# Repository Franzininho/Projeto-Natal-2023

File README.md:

# Projeto Natal 2023 Comunidade Franzininho

Esse é um projeto de placa decorativa de natal baseada no MCU Risc V CH32V003

## Requisitos 
 - MCU CH32V003F4P6
 - Alimentação por bateria CR2032
 - Animação em LEDs ou outra interface gráfica
 - Projeto no Kicad
 - Outros: Botão, buzzer, etc

## Como Participar?
1. Crie um fork desse projeto base.
2. Faça o seu Desing
3. Crie uma pequena documentação para explicar o seu projeto
4. Envie seu projeto para a comunidade Franzininho

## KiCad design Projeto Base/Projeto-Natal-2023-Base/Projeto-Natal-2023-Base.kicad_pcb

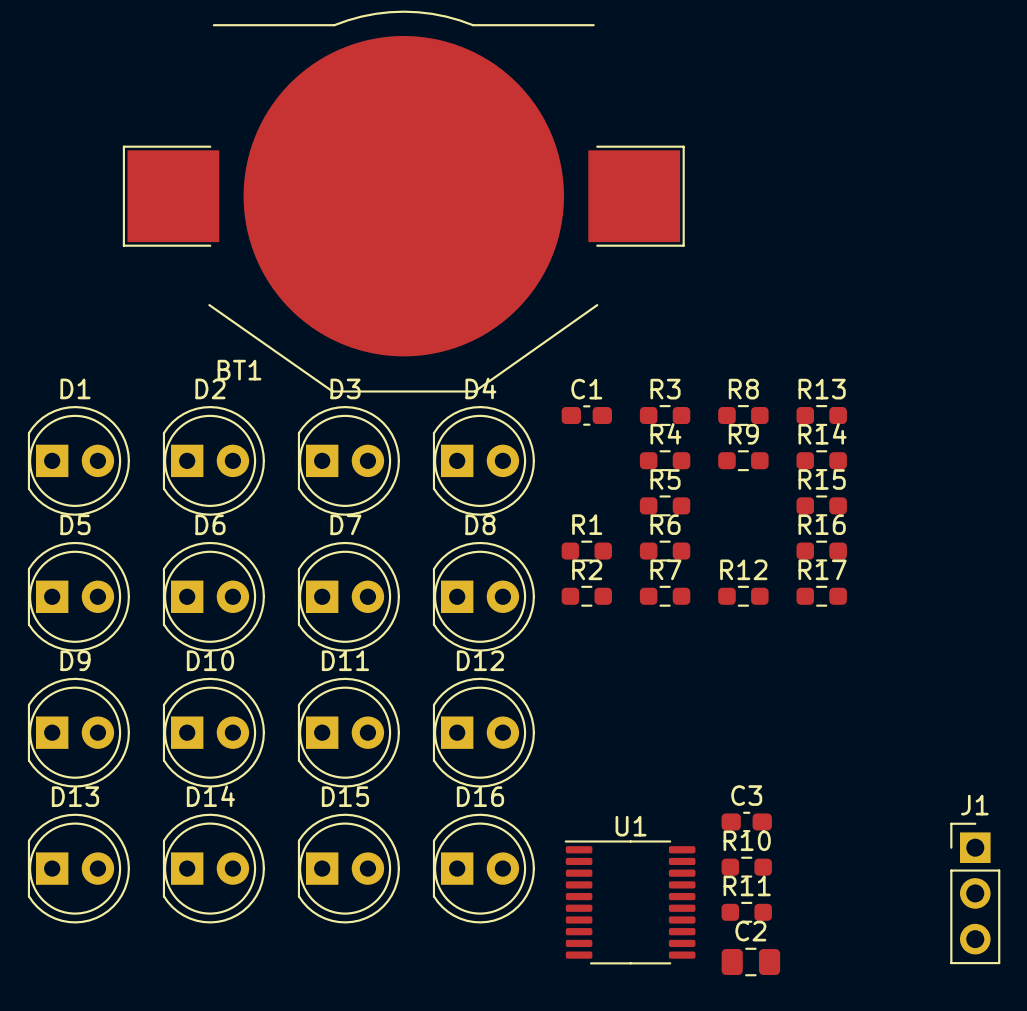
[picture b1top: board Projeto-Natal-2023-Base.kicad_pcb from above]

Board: 2 copper layers, 39 parts (0 on the bottom side), 34 nets, no tracks yet.

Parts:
BT1: Battery_Cell; BatteryHolder_Keystone_3002_1x2032
C1, C3: 100nF; C_0603_1608Metric_Pad1.08x0.95mm_HandSolder
C2: 10uF; C_0805_2012Metric_Pad1.18x1.45mm_HandSolder
D1, D2, D3, D4: LED R; LED_D5.0mm
D5, D6, D7, D8: LED G; LED_D5.0mm
D9, D10, D11, D12: LED B; LED_D5.0mm
D13, D14, D15, D16: LED Y; LED_D5.0mm
J1: Conn_01x03_Pin; PinHeader_1x03_P2.54mm_Vertical
R1: 10K; R_0603_1608Metric_Pad0.98x0.95mm_HandSolder
R2, R3, R4, R5, R6, R7, R8, R9, R10, R11, R12, R13, R14, R15, R16, R17: 1K; R_0603_1608Metric_Pad0.98x0.95mm_HandSolder
U1: CH32V003F4P6; TSSOP-20_4.4x6.5mm_P0.65mm

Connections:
+3V3: BT1.1 (+), C2.1, C3.2, J1.1, R1.1, U1.9 (VDD)
GND: BT1.2 (-), C1.1, C2.2, C3.1, D1.1 (K), D2.1 (K), D3.1 (K), D4.1 (K), D5.1 (K), D6.1 (K), D7.1 (K), D8.1 (K), D9.1 (K), D10.1 (K), D11.1 (K), D12.1 (K), D13.1 (K), D14.1 (K), D15.1 (K), D16.1 (K), J1.2, U1.7 (VSS)
LED1: D1.2 (A), R2.1
LED2: D5.2 (A), R3.1
LED3: D9.2 (A), R4.1
LED4: D13.2 (A), R5.1
LED5: D2.2 (A), R6.1
LED6: D6.2 (A), R7.1
LED7: D10.2 (A), R8.1
LED8: D14.2 (A), R9.1
LED11: D11.2 (A), R10.2, R11.2, R12.2
LED12: D15.2 (A), R13.2
LED13: D4.2 (A), R14.2
LED14: D8.2 (A), R15.2
LED15: D12.2 (A), R16.2
LED16: D16.2 (A), R17.2
unnamed: C1.2, R1.2, U1.4 (NRST/PD7)
unnamed: R2.2, U1.5 (OSC_IN/PA1)
unnamed: R3.2, U1.6 (OSC_OUT/PA2)
unnamed: R10.1, U1.10 (PC0)
unnamed: R11.1, U1.11 (PC1)
unnamed: R12.1, U1.12 (PC2)
unnamed: R13.1, U1.13 (PC3)
unnamed: R14.1, U1.14 (PC4)
unnamed: R15.1, U1.15 (PC5)
unnamed: R16.1, U1.16 (PC6)
unnamed: R17.1, U1.17 (PC7)
unnamed: R4.2, U1.8 (PD0)
unnamed: R5.2, U1.19 (PD2)
unnamed: R6.2, U1.20 (PD3)
unnamed: R7.2, U1.1 (PD4)
unnamed: R8.2, U1.2 (PD5)
unnamed: R9.2, U1.3 (PD6)
SWIO: J1.3, U1.18 (PD1)

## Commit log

2023-11-09 Inclusão de esboço inicial do projeto base.
2023-11-09 trocando mcu para ch32v003f4p6
2023-11-09 Adicionando conector de SWIO
